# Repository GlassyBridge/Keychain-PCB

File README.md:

# Keychain-PCB
My first PCB design. Made for solder at hackclub, a challenge that requires the partticipants to build a PCB using limited components.
It is a Keychain based on my PFP(profile picture) on hackclub's slack, @GB114.
## Features
- Two LEDs that light up when SW1 is pressed.
  - Photoresistor with transistor(NPN) to not turn on the LEDs in bright environments.
- DC_Motor(Vibrator) that vibrates when SW2 is pressed.
  - The intensity is adjustable by a potentiometer.
## How to get yours?
- Just take the gerber.zip file from the production folder and give it to your manufacturer. (or manufacture it yourself.)
## BOM (Bill of Materials)
| Material        | Footprint                                  | Quantity | Types |
|-----------------|--------------------------------------------|----------|-------|
| Battery holder  | BatteryHolder_Keystone_3034_1x20mm         | 1        |       |
| LEDs            | LED_D5.0mm                                 | 2        |       |
| DC_Motor        | PinHeader_1x02_P2.54mm_Vertical            | 1        |       |
| Transistor(NPN) | TO-92L_HandSolder                          | 1        |       |
| Resistors       | R_Axial_DIN0207_L6.3mm_D2.5mm_P7.62mm_Horizontal | 7        | 6 - 220Ω, 1 - 4.7kΩ |
| R_Photo         | R_LDR_5.1x4.3mm_P3.4mm_Vertical            | 1        |       |
| Potentiometer   | Potentiometer_Vishay_T73YP_Vertical        | 1        |       |
| Push buttons    | SW_PUSH_6mm                                | 2        |       |

## Schematics

## PCB

## 3D view

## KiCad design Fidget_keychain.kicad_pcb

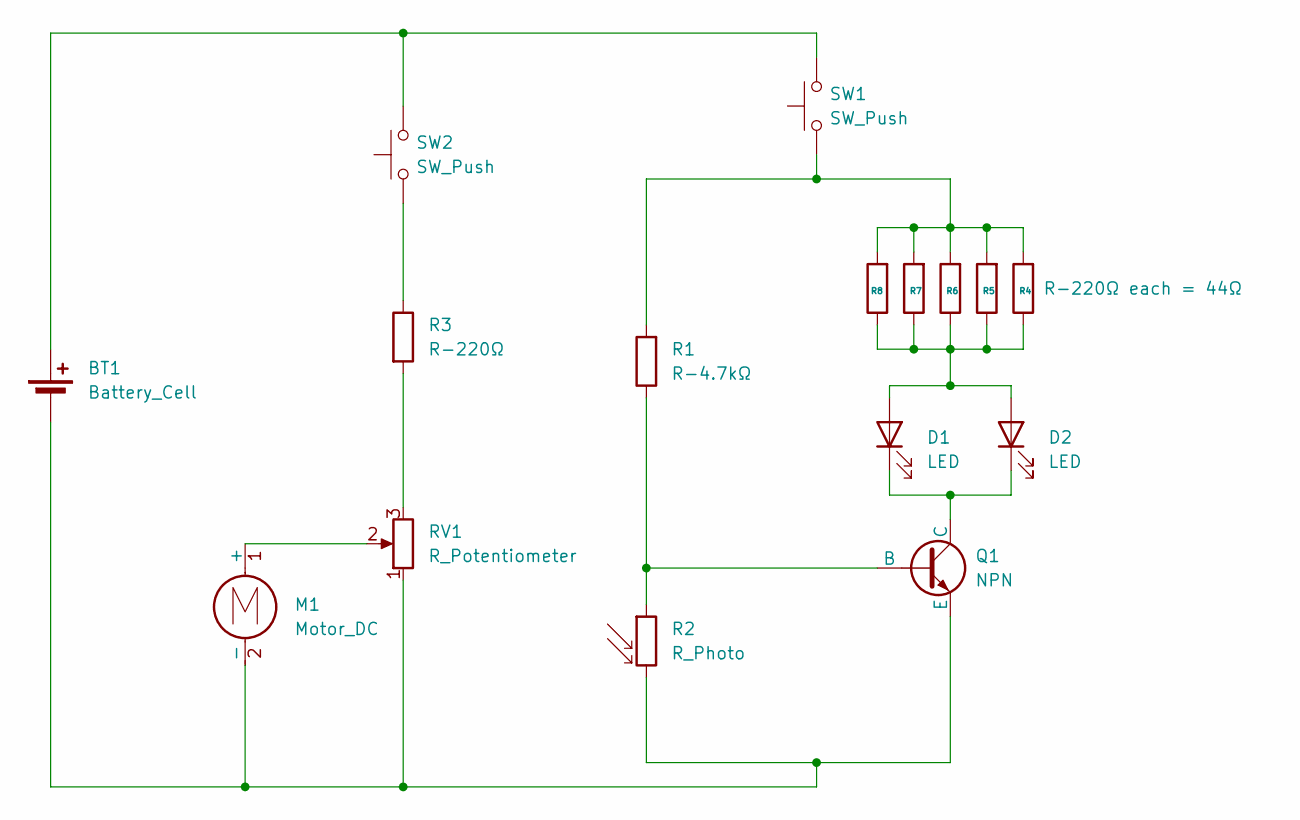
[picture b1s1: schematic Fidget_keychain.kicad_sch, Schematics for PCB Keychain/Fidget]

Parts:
BT1: Battery_Cell; BatteryHolder_Keystone_3034_1x20mm
D1, D2: LED; LED_D5.0mm
M1: Motor_DC; PinHeader_1x02_P2.54mm_Vertical
Q1: NPN; TO-92L_HandSolder
R1: R-4.7kΩ; R_Axial_DIN0207_L6.3mm_D2.5mm_P7.62mm_Horizontal
R2: R_Photo; R_LDR_5.1x4.3mm_P3.4mm_Vertical
R3: R-220Ω; R_Axial_DIN0207_L6.3mm_D2.5mm_P7.62mm_Horizontal
R4: R-220Ω each = 44Ω; R_Axial_DIN0207_L6.3mm_D2.5mm_P7.62mm_Horizontal
R5, R6, R7, R8: R_Axial_DIN0207_L6.3mm_D2.5mm_P7.62mm_Horizontal
RV1: R_Potentiometer; Potentiometer_Vishay_T73YP_Vertical
SW1, SW2: SW_Push; SW_PUSH_6mm

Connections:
unnamed: BT1.1 (+), SW1.2, SW2.2
unnamed: BT1.2 (-), M1.2 (-), Q1.3 (E), R2.2, RV1.1
unnamed: D1.2 (A), D2.2 (A), R4.1, R5.1, R6.1, R7.1, R8.1
unnamed: D1.1 (K), D2.1 (K), Q1.1 (C)
unnamed: M1.1 (+), RV1.2
unnamed: Q1.2 (B), R1.1, R2.1
unnamed: R1.2, R4.2, R5.2, R6.2, R7.2, R8.2, SW1.1
unnamed: R3.1, SW2.1
unnamed: R3.2, RV1.3

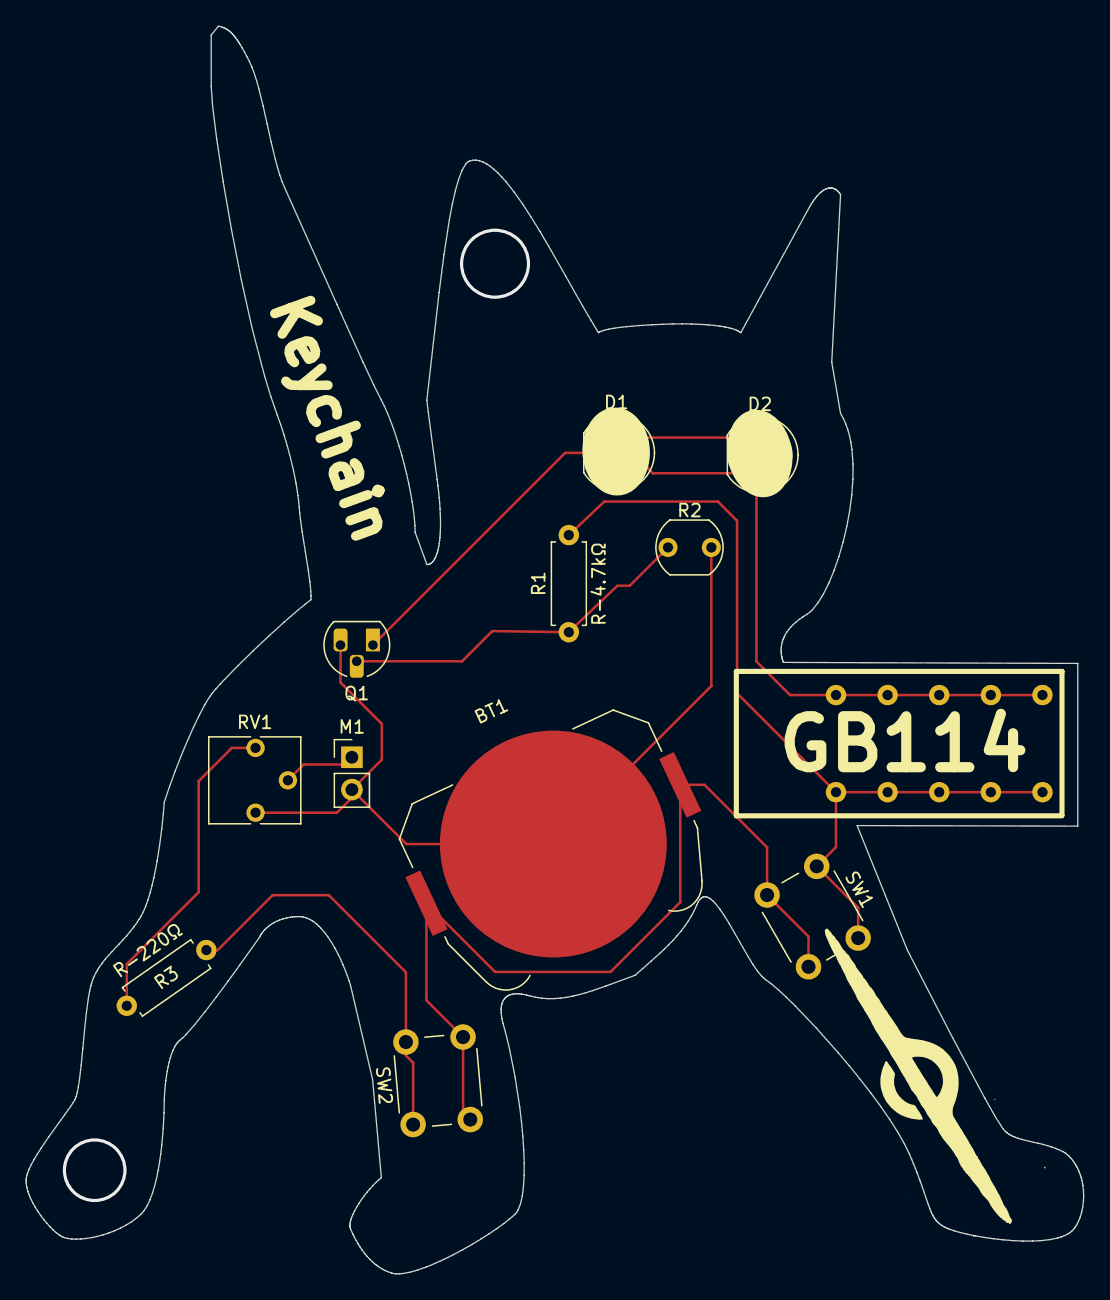
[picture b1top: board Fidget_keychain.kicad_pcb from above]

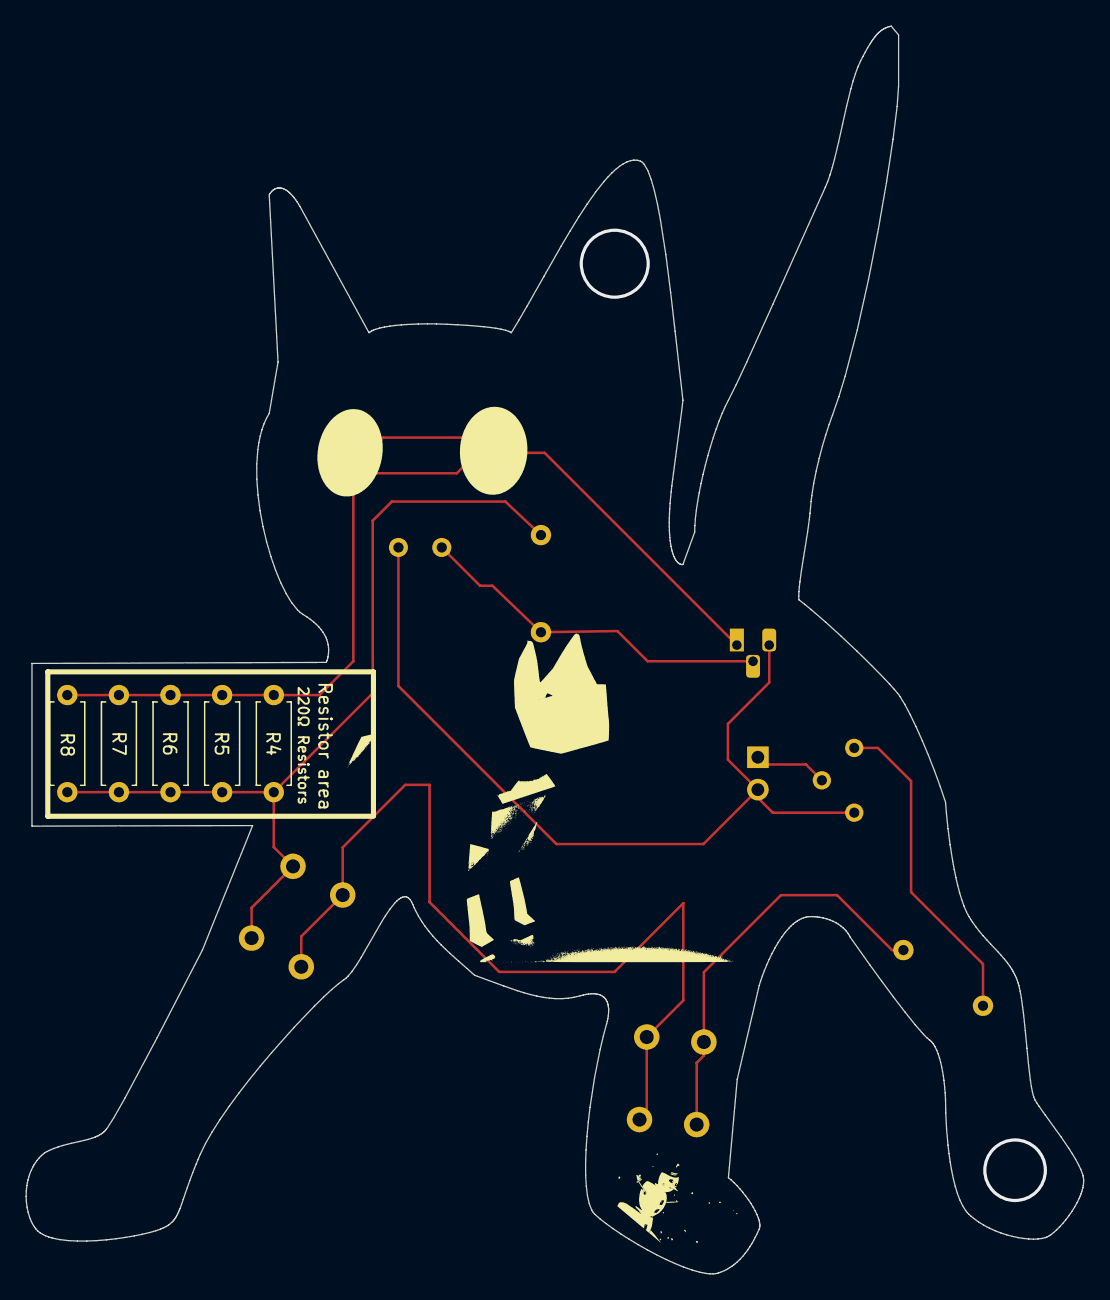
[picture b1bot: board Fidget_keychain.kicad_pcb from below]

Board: 2 copper layers, 83.0 x 97.9 mm, 16 parts (5 on the bottom side), 9 nets.

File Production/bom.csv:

Designator,Footprint,Quantity,Value,LCSC Part #
BT1,BatteryHolder_Keystone_3034_1x20mm,1,Battery_Cell,
"D1, D2",LED_D5.0mm,2,LED,
M1,PinHeader_1x02_P2.54mm_Vertical,1,Motor_DC,
Q1,TO-92L_HandSolder,1,NPN,
R1,R_Axial_DIN0207_L6.3mm_D2.5mm_P7.62mm_Horizontal,1,R-4.7kΩ,
R2,R_LDR_5.1x4.3mm_P3.4mm_Vertical,1,R_Photo,
"R3,R4,R5, R6, R7, R8",R_Axial_DIN0207_L6.3mm_D2.5mm_P7.62mm_Horizontal,6,R-220Ω,
RV1,Potentiometer_Vishay_T73YP_Vertical,1,R_Potentiometer,
"SW1, SW2",SW_PUSH_6mm,2,SW_Push,

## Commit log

2025-06-23 Project file
2025-06-23 PCB & PRL
2025-06-23 schematics
2025-06-23 Create NONE
2025-06-24 Added pro,pcb and schematic files
2025-06-24 Added images via upload
2025-06-24 Added images
2025-07-03 Added Gerber.zip
    For production purposes. (You can send this to manufacturers.)
